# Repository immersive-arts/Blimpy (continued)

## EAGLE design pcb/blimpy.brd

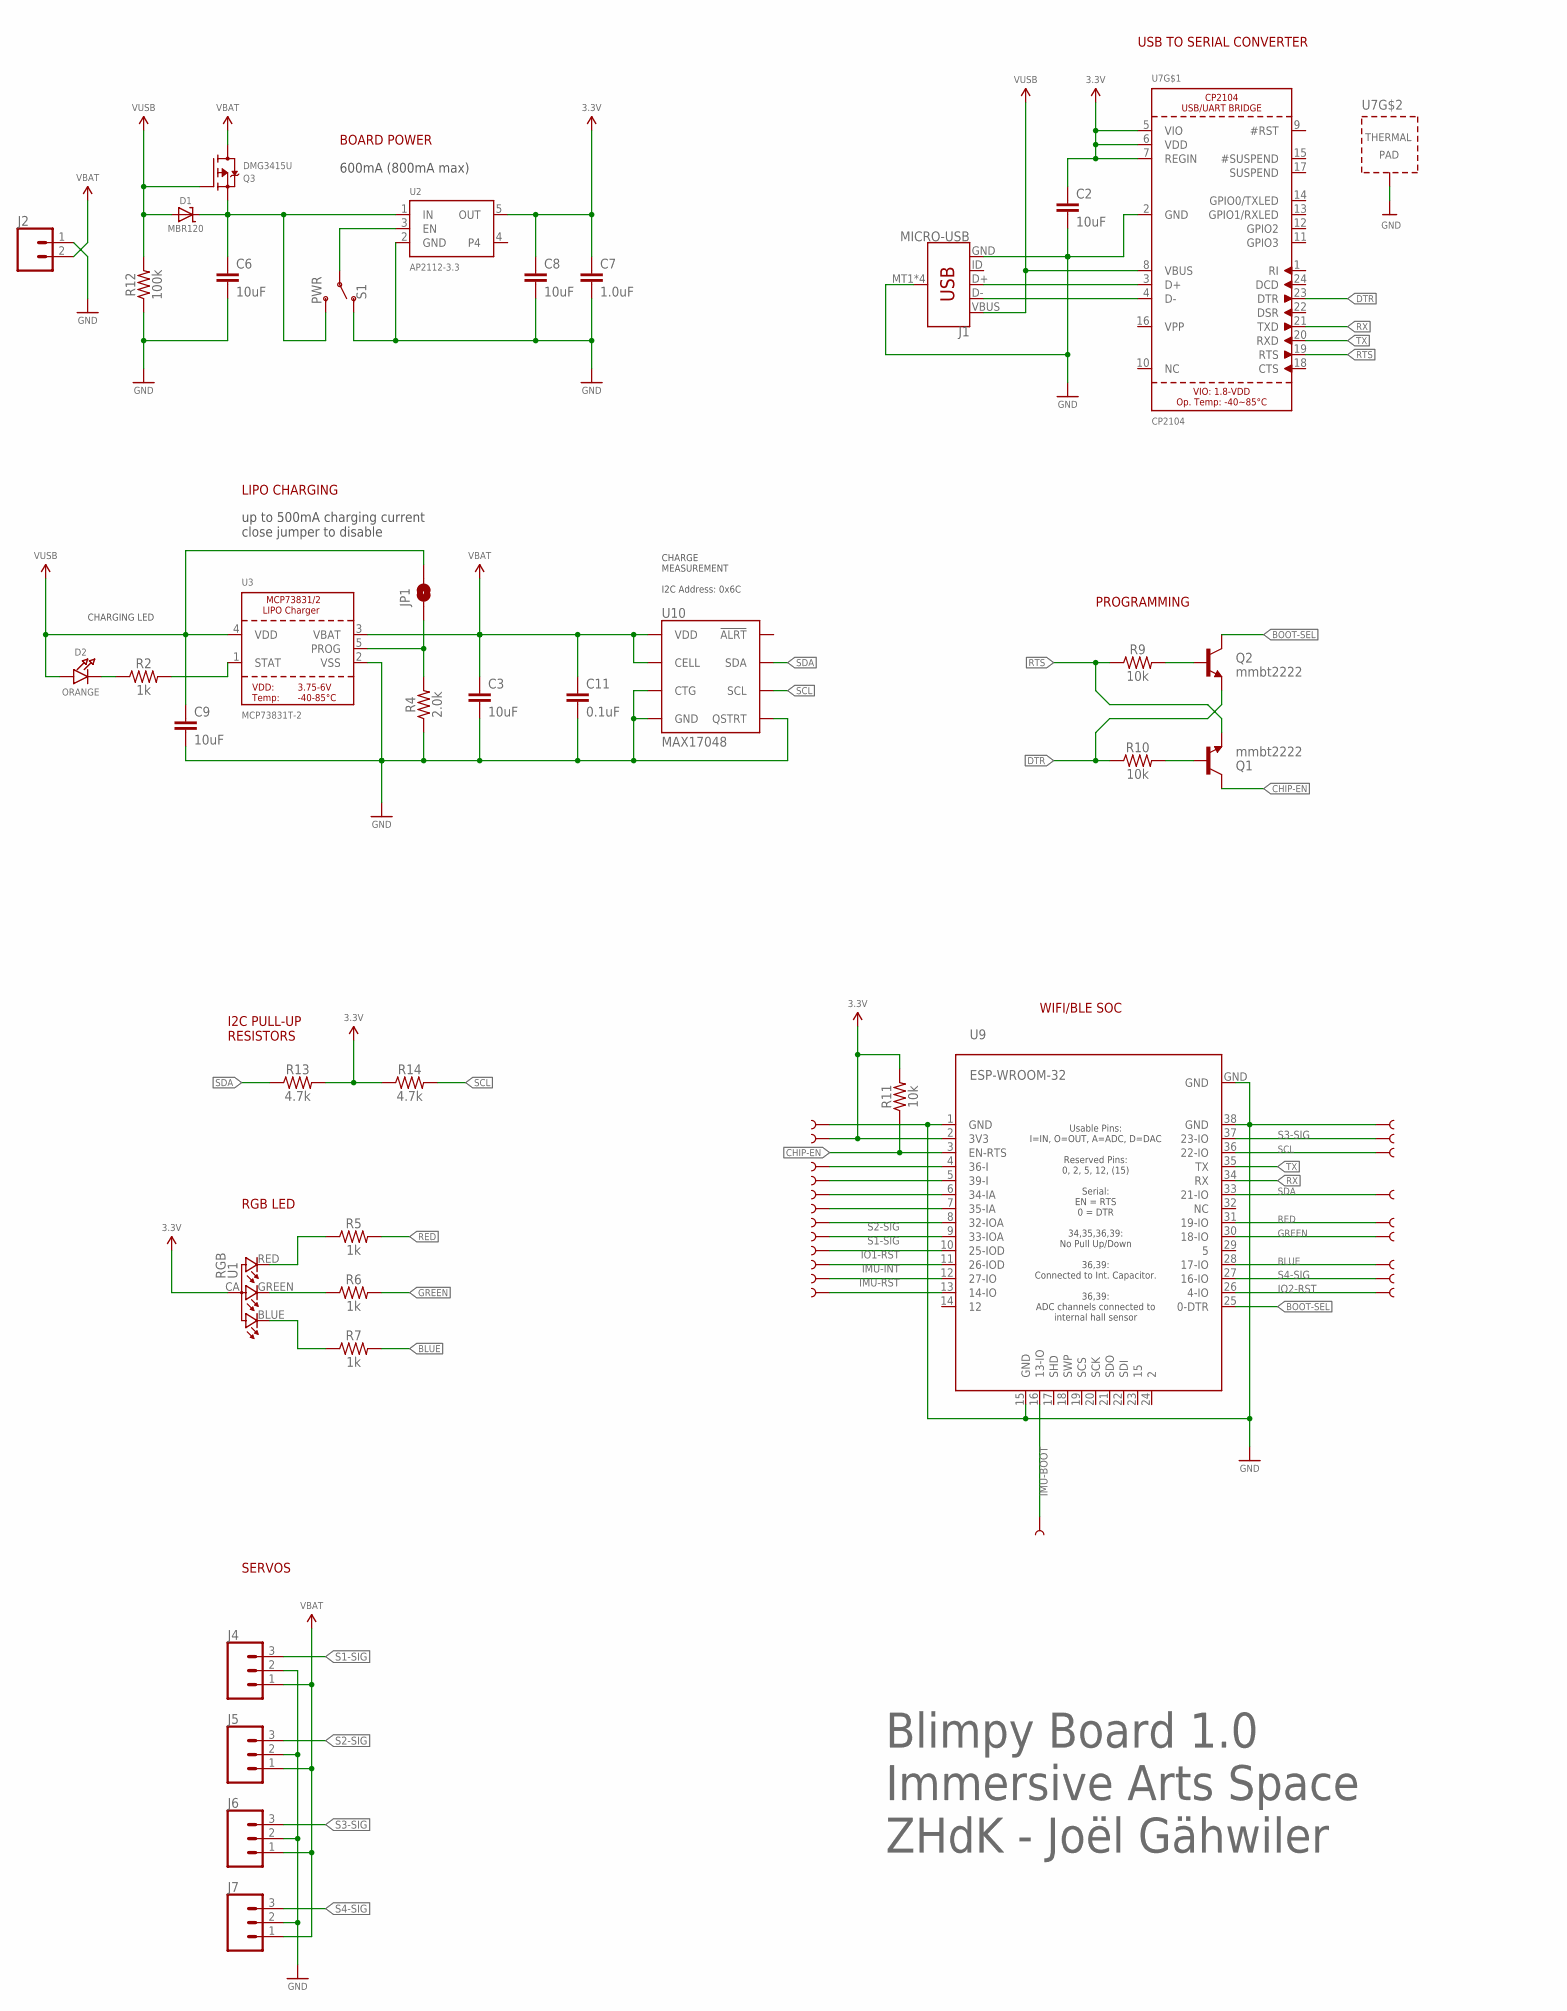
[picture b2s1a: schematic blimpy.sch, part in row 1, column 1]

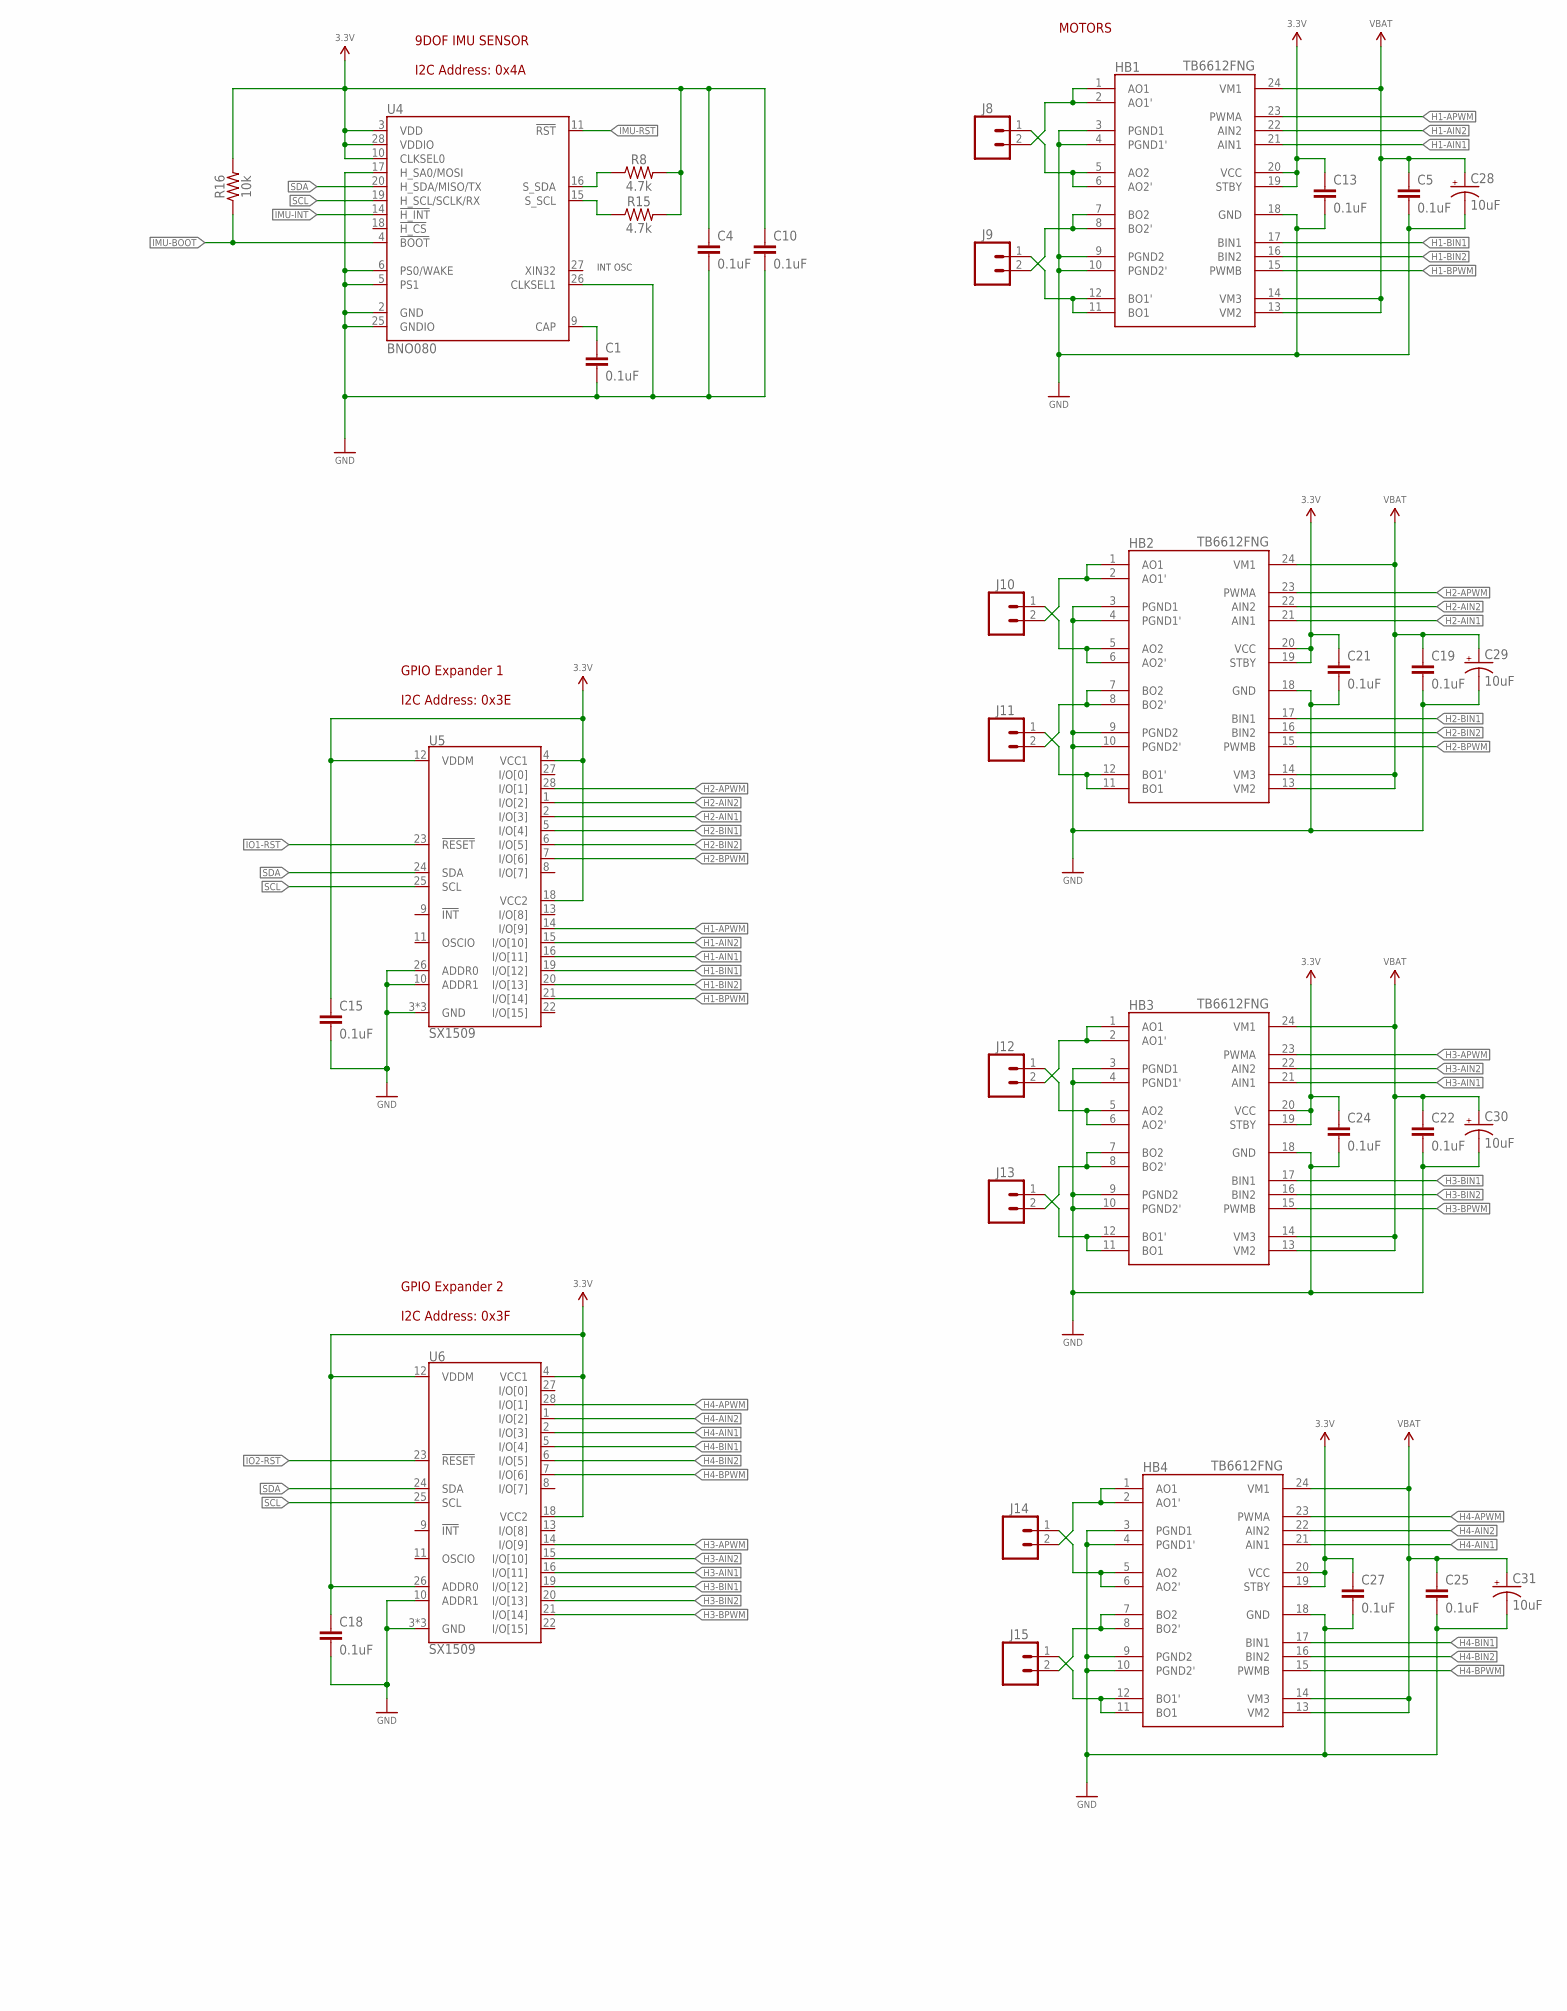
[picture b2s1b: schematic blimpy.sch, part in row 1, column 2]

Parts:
C1, C4, C5, C10, C11, C13, C15, C18, C19, C21, C22, C24, C25, C27: 0.1uF; 0603
C2, C3, C6, C8, C9: 10uF; 0603
C7: 1.0uF; 0603
C28, C29, C30, C31: 10uF; EIA3216
D1: MBR120; SOD-123
D2: ORANGE; CHIPLED_0805_NOOUTLINE
HB1, HB2, HB3, HB4: TB6612FNG; SSOP24
J1: MICRO-USB; USB-MICROB
J2, J8, J9, J10, J11, J12, J13, J14, J15: CONN_02-JST-2MM-SMT; JST-2-SMD
J4, J5, J6, J7: 3-PIN SMD; JST-3-SMD
JP1: JUMPER-SMT_2_NO_SILK; SMT-JUMPER_2_NO_SILK
Q1, Q2: mmbt2222; SOT23-3
Q3: DMG3415U; SOT23-R
R2, R5, R6, R7: 1k; 0603
R4: 2.0k; 0603
R8, R13, R14, R15: 4.7k; 0603
R9, R10, R11, R16: 10k; 0603
R12: 100k; 0603
S1: PWR; SWITCH_SPST_SMD_A
TP1, TP2, TP3, TP4, TP5, TP6, TP7, TP8, TP9, TP10, TP11, TP12, TP13, TP14, TP15, TP16, TP17, TP18, TP19, TP20, TP21, TP22: TEST-POINT3; PAD.03X.03
U1: RGB; PLCC4-2MM-RGB
U2: AP2112-3.3; SOT23-5
U3: MCP73831T-2; SOT23-5
U4: BNO080; LGA-28
U5, U6: SX1509; QFN-28
U7: CP2104; QFN24_4MM_SMSC
U9: ESP-WROOM-32
U10: MAX17048; DFN-8

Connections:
3.3V: C2.1, C4.1, C7.1, C8.1, C10.1, C13.1, C15.1, C18.1, C21.1, C24.1, C27.1, HB1.19 (STBY), HB1.20 (VCC), HB2.19 (STBY), HB2.20 (VCC), HB3.19 (STBY), HB3.20 (VCC), HB4.19 (STBY), HB4.20 (VCC), R8.2, R11.2, R13.2, R14.1, R15.2, R16.2, TP11.P$1, U1.CA (1), U2.5 (OUT), U4.3 (VDD), U4.10 (CLKSEL0), U4.28 (VDDIO), U5.4 (VCC1), U5.12 (VDDM), U5.18 (VCC2), U6.4 (VCC1), U6.12 (VDDM), U6.18 (VCC2), U6.26 (ADDR0), U7.5 (VIO), U7.6 (VDD), U7.7 (REGIN), U9.2 (3V3)
BLUE: R7.2, TP22.P$1, U9.28 (17-IO)
BOOT-SEL: Q2.3 (C), U9.25 (0-DTR)
CHIP-EN: Q1.3 (C), R11.1, U9.3 (EN-RTS)
DTR: Q2.2 (E), R10.1, U7.23 (DTR)
GND: C1.2, C2.2, C3.2, C4.2, C5.2, C6.2, C7.2, C8.2, C9.2, C10.2, C11.2, C13.2, C15.2, C18.2, C19.2, C21.2, C22.2, C24.2, C25.2, C27.2, C28.-, C29.-, C30.-, C31.-, HB1.3 (PGND1), HB1.4 (PGND1'), HB1.9 (PGND2), HB1.10 (PGND2'), HB1.18 (GND), HB2.3 (PGND1), HB2.4 (PGND1'), HB2.9 (PGND2), HB2.10 (PGND2'), HB2.18 (GND), HB3.3 (PGND1), HB3.4 (PGND1'), HB3.9 (PGND2), HB3.10 (PGND2'), HB3.18 (GND), HB4.3 (PGND1), HB4.4 (PGND1'), HB4.9 (PGND2), HB4.10 (PGND2'), HB4.18 (GND), J1.GND, J1.MT1 (SHIELD), J1.MT2 (SHIELD), J1.P$1 (SHIELD), J1.P$2 (SHIELD), J2.1 (2), J4.2, J5.2, J6.2, J7.2, R4.1, R12.1, S1.1 (O), TP12.P$1, TP13.P$1, U2.2 (GND), U3.2 (VSS), U4.2 (GND), U4.5 (PS1), U4.6 (PS0/WAKE), U4.17 (H_SA0/MOSI), U4.25 (GNDIO), U4.26 (CLKSEL1), U5.3 (GND), U5.10 (ADDR1), U5.17 (GND), U5.26 (ADDR0), U5.29 (GND), U6.3 (GND), U6.10 (ADDR1), U6.17 (GND), U6.29 (GND), U7.2 (GND), U7.THERM (TP), U9.1 (GND), U9.15 (GND), U9.38 (GND), U9.GND, U10.P$1 (CTG), U10.P$4 (GND), U10.P$6 (QSTRT), U10.P$9 (GND)
GREEN: R6.2, TP21.P$1, U9.30 (18-IO)
H1-AIN1: HB1.21 (AIN1), U5.16 (I/O[11])
H1-AIN2: HB1.22 (AIN2), U5.15 (I/O[10])
H1-APWM: HB1.23 (PWMA), U5.14 (I/O[9])
H1-BIN1: HB1.17 (BIN1), U5.19 (I/O[12])
H1-BIN2: HB1.16 (BIN2), U5.20 (I/O[13])
H1-BPWM: HB1.15 (PWMB), U5.21 (I/O[14])
H2-AIN1: HB2.21 (AIN1), U5.2 (I/O[3])
H2-AIN2: HB2.22 (AIN2), U5.1 (I/O[2])
H2-APWM: HB2.23 (PWMA), U5.28 (I/O[1])
H2-BIN1: HB2.17 (BIN1), U5.5 (I/O[4])
H2-BIN2: HB2.16 (BIN2), U5.6 (I/O[5])
H2-BPWM: HB2.15 (PWMB), U5.7 (I/O[6])
H3-AIN1: HB3.21 (AIN1), U6.16 (I/O[11])
H3-AIN2: HB3.22 (AIN2), U6.15 (I/O[10])
H3-APWM: HB3.23 (PWMA), U6.14 (I/O[9])
H3-BIN1: HB3.17 (BIN1), U6.19 (I/O[12])
H3-BIN2: HB3.16 (BIN2), U6.20 (I/O[13])
H3-BPWM: HB3.15 (PWMB), U6.21 (I/O[14])
H4-AIN1: HB4.21 (AIN1), U6.2 (I/O[3])
H4-AIN2: HB4.22 (AIN2), U6.1 (I/O[2])
H4-APWM: HB4.23 (PWMA), U6.28 (I/O[1])
H4-BIN1: HB4.17 (BIN1), U6.5 (I/O[4])
H4-BIN2: HB4.16 (BIN2), U6.6 (I/O[5])
H4-BPWM: HB4.15 (PWMB), U6.7 (I/O[6])
HB1-A1: HB1.1 (AO1), HB1.2 (AO1'), J8.2 (1)
HB1-A2: HB1.5 (AO2), HB1.6 (AO2'), J8.1 (2)
HB1-B1: HB1.11 (BO1), HB1.12 (BO1'), J9.1 (2)
HB1-B2: HB1.7 (BO2), HB1.8 (BO2'), J9.2 (1)
HB2-A1: HB2.1 (AO1), HB2.2 (AO1'), J10.2 (1)
HB2-A2: HB2.5 (AO2), HB2.6 (AO2'), J10.1 (2)
HB2-B1: HB2.11 (BO1), HB2.12 (BO1'), J11.1 (2)
HB2-B2: HB2.7 (BO2), HB2.8 (BO2'), J11.2 (1)
HB3-A1: HB3.1 (AO1), HB3.2 (AO1'), J12.2 (1)
HB3-A2: HB3.5 (AO2), HB3.6 (AO2'), J12.1 (2)
HB3-B1: HB3.11 (BO1), HB3.12 (BO1'), J13.1 (2)
HB3-B2: HB3.7 (BO2), HB3.8 (BO2'), J13.2 (1)
HB4-A1: HB4.1 (AO1), HB4.2 (AO1'), J14.2 (1)
HB4-A2: HB4.5 (AO2), HB4.6 (AO2'), J14.1 (2)
HB4-B1: HB4.11 (BO1), HB4.12 (BO1'), J15.1 (2)
HB4-B2: HB4.7 (BO2), HB4.8 (BO2'), J15.2 (1)
IMU-BOOT: R16.1, TP17.P$1, U4.4 (!BOOT), U9.16 (13-IO)
IMU-INT: TP4.P$1, U4.14 (!H_INT), U9.11 (26-IOD)
IMU-RST: TP5.P$1, U4.11 (!RST), U9.12 (27-IO)
IO1-RST: TP3.P$1, U5.23 (!RESET), U9.10 (25-IOD)
IO2-RST: TP16.P$1, U6.23 (!RESET), U9.26 (4-IO)
unnamed: D2.C, R2.1
unnamed: J1.D+, U7.3 (D+)
unnamed: R2.2, U3.1 (STAT)
unnamed: JP1.1, R4.2, U3.5 (PROG)
unnamed: J1.D-, U7.4 (D-)
unnamed: C6.1, D1.C, Q3.2 (S), S1.3 (S), U2.1 (IN)
unnamed: S1.2, U2.3 (EN)
unnamed: R5.1, U1.RED (4)
unnamed: R7.1, U1.BLUE (2)
unnamed: R6.1, U1.GREEN (3)
unnamed: Q1.1 (B), R10.2
unnamed: Q2.1 (B), R9.2
unnamed: R8.1, U4.16 (S_SDA)
unnamed: R15.1, U4.15 (S_SCL)
unnamed: C1.1, U4.9 (CAP)
unnamed: TP10.P$1, U9.4 (36-I)
unnamed: TP9.P$1, U9.5 (39-I)
unnamed: TP8.P$1, U9.6 (34-IA)
unnamed: TP7.P$1, U9.7 (35-IA)
unnamed: TP6.P$1, U9.13 (14-IO)
RED: R5.2, TP20.P$1, U9.31 (19-IO)
RTS: Q1.2 (E), R9.1, U7.19 (RTS)
RX: U7.21 (TXD), U9.34 (RX)
S1-SIG: J4.3, TP2.P$1, U9.9 (33-IOA)
S2-SIG: J5.3, TP1.P$1, U9.8 (32-IOA)
S3-SIG: J6.3, TP14.P$1, U9.37 (23-IO)
S4-SIG: J7.3, TP15.P$1, U9.27 (16-IO)
SCL: R14.2, TP18.P$1, U4.19 (H_SCL/SCLK/RX), U5.25 (SCL), U6.25 (SCL), U9.36 (22-IO), U10.P$7 (SCL)
SDA: R13.1, TP19.P$1, U4.20 (H_SDA/MISO/TX), U5.24 (SDA), U6.24 (SDA), U9.33 (21-IO), U10.P$8 (SDA)
TX: U7.20 (RXD), U9.35 (TX)
V_BATT: C3.1, C5.1, C11.1, C19.1, C22.1, C25.1, C28.+, C29.+, C30.+, C31.+, HB1.13 (VM2), HB1.14 (VM3), HB1.24 (VM1), HB2.13 (VM2), HB2.14 (VM3), HB2.24 (VM1), HB3.13 (VM2), HB3.14 (VM3), HB3.24 (VM1), HB4.13 (VM2), HB4.14 (VM3), HB4.24 (VM1), J2.2 (1), J4.1, J5.1, J6.1, J7.1, Q3.3 (D), U3.3 (VBAT), U10.P$2 (CELL), U10.P$3 (VDD)
V_USB: C9.1, D1.A, D2.A, J1.VBUS, JP1.2, Q3.1 (G), R12.2, U3.4 (VDD), U7.8 (VBUS)

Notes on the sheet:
BOARD POWER
up to 500mA charging current close jumper to disable
USB TO SERIAL CONVERTER
LIPO CHARGING
RGB LED
PROGRAMMING
CHARGING LED
CHARGE MEASUREMENT I2C Address: 0x6C
I2C PULL-UP RESISTORS
WIFI/BLE SOC
9DOF IMU SENSOR I2C Address: 0x4A
INT OSC
GPIO Expander 1 I2C Address: 0x3E
GPIO Expander 2 I2C Address: 0x3F
600mA (800mA max)
SERVOS
MOTORS
Blimpy Board 1.0 Immersive Arts Space ZHdK - Joël Gähwiler

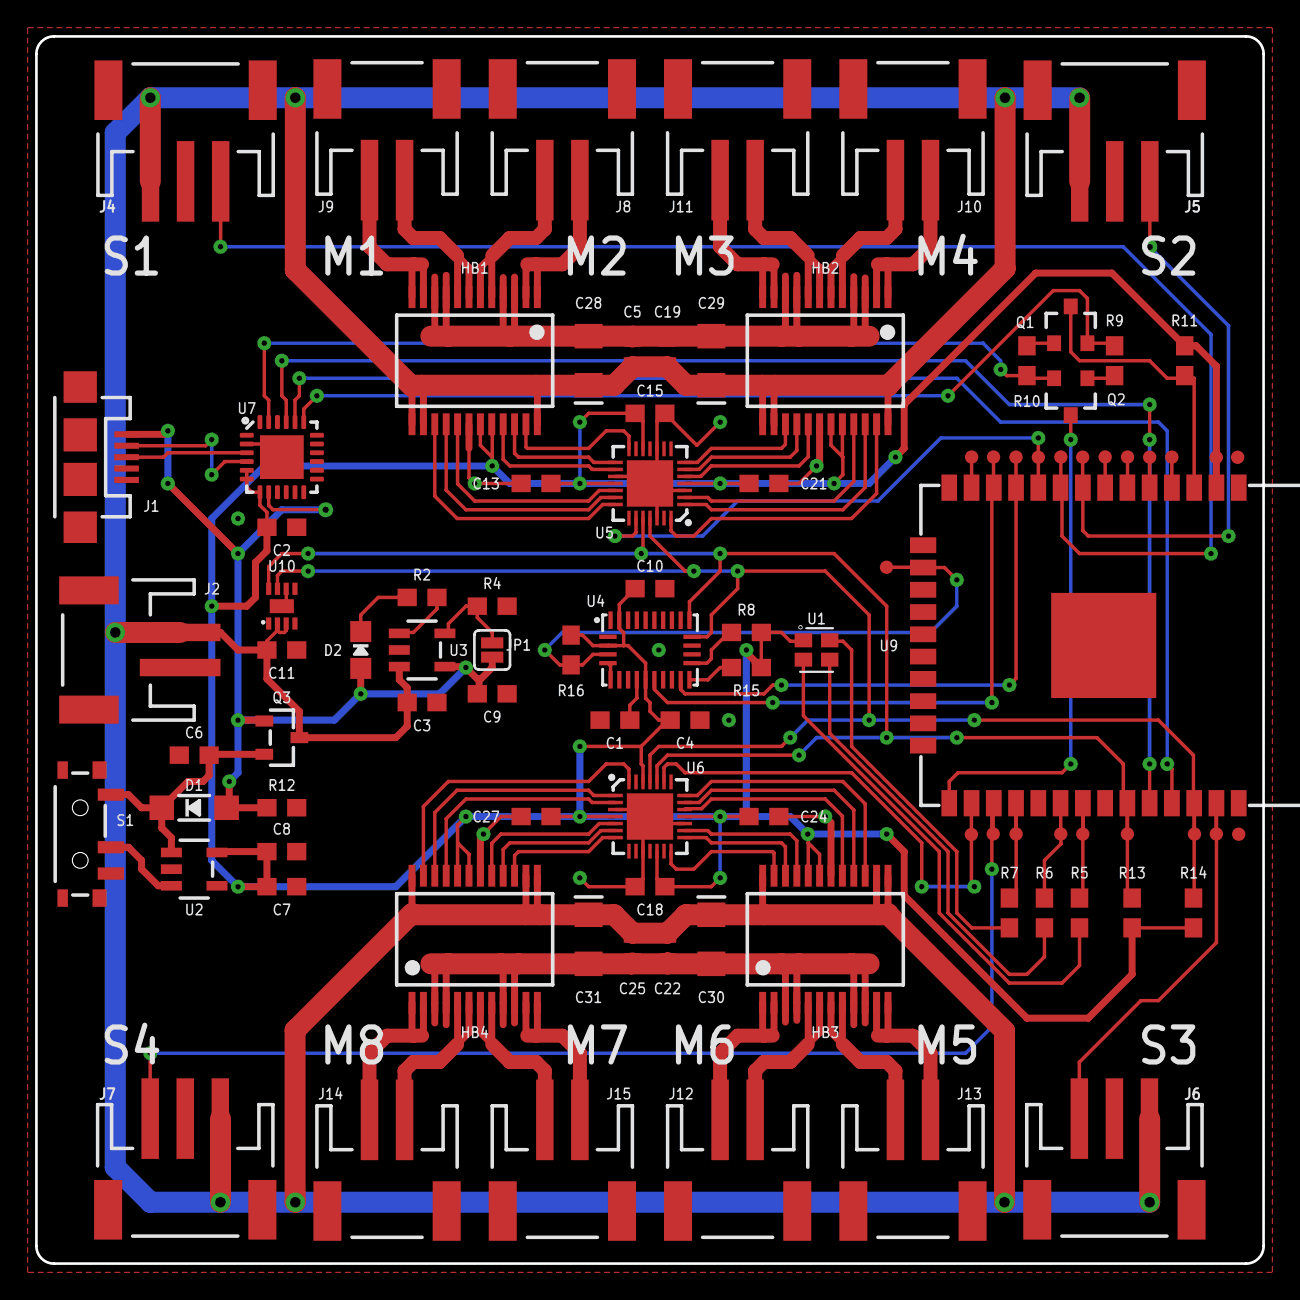
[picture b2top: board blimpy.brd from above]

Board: 2 copper layers, 70.0 x 70.0 mm, 94 parts (0 on the bottom side), 84 nets.

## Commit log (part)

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2019-07-19 added wifi and battery indicators
2019-07-20 fix null pointer
2019-09-12 first pcb iteration
2019-09-13 added settings
2019-09-13 de-invert
2019-09-13 added logo
2019-09-18 updated board design
2019-09-18 added battery gauge
2019-09-18 added address
2019-09-19 removed todo
2019-09-26 improved hbridge traces
2019-09-26 added hbridge gnd traces
2019-09-26 updated hbridge traces and prepared expander
2019-09-26 use 0.2mm traces
2019-09-26 wired io and caps
2019-09-26 fixed io capacitors
2019-09-26 finished hbridge io
2019-09-26 small connections
2019-09-26 updated labels
2019-09-26 reworked main connectors
2019-09-26 downgraded version
2019-09-26 changed setting keys
2019-09-26 replaced usb micro with usb c connector
2019-09-27 shrinked board
2019-09-27 moved stuff into place
2019-09-27 fixed size
2019-09-27 fixed servo pins
2019-09-27 moved in auxillary components
2019-09-27 small fix
2019-09-27 connect imu
2019-09-27 more traces
2019-09-27 show all
2019-09-27 small fixes
2019-09-27 more fixes
2019-09-27 updated vias
2019-09-27 more power traces
2019-09-27 improved power routing
2019-09-27 hide some layers
2019-09-27 connected all components
2019-09-27 finished all traces
2019-09-28 added ground plane and fixed all errors
2019-09-28 changed colors
2019-09-28 fixed
2019-09-28 moved esp
2019-09-28 added text
2019-09-28 updated todo
2019-09-29 routed pogo pins
2019-09-29 moved docs
2019-09-29 bigger ground pads on h bridges
2019-09-29 optimized main battery connections
2019-09-29 rerouted io1-rst
2019-09-29 reduced space
2019-09-29 made more space
2019-09-29 moved led to middle
2019-09-29 updated bom
2019-09-29 added more pogo pins
2019-09-29 added prices
2019-09-30 removed obsolete resistors
2019-09-30 updated docs
2019-09-30 fixed typo
2019-09-30 added awg 28 info
2019-10-07 changed schotky diode to BAT20J
2019-10-07 updated part numbers
2019-10-22 fixed onboard model
2019-10-24 removed not needed duty cycle
2019-10-24 print more stuff
2019-10-24 prototype onboard model calculation
2019-10-24 fix strtok overflow
2019-10-24 free objects
2019-10-24 added comment
2019-10-24 read configuration from parameters
2019-10-24 fix configs
2019-10-24 flip matrix
2019-11-17 read fuel gauge
2019-11-18 new motor control
2019-11-18 disable pullup
2019-11-20 added two motors to model
2019-11-20 use on-board model
2019-11-20 correct controls
2019-11-20 constrain before printing
2019-11-21 added min duty and print fault
2019-11-22 finish dynamic model calculations
2019-11-22 fix model
2019-11-22 use onboard model for calculations
2019-11-23 fix bug
2019-11-25 added servo control
2019-11-25 adde pdfs
2019-11-25 new repo architecture
2019-12-05 prototype manager api
2019-12-09 added max sparck patcher for testing flightpaths
2019-12-12 new speed data fo the drones
2019-12-17 added base topic setting
2019-12-17 choreography three paths
2019-12-17 updated firmware readme
2019-12-17 docs for fanhousing
2019-12-17 mit gif
2019-12-17 updated apps/max and formware documentation
2019-12-17 new pics and main readme
2019-12-17 update pix
2019-12-17 documentation almost finshed. folder name change
2019-12-17 updated main readme
2019-12-17 fanmount print insctructions complete
2019-12-17 gif links added
2019-12-17 new path forms
2019-12-17 path updates
2019-12-18 Added manager
2019-12-18 Added scripts
2019-12-19 Added readme to Manager
2019-12-19 API adjustments
2019-12-20 updated mainreadme
2019-12-20 moved logo to assets
2019-12-20 manager readme adjustments
2019-12-20 added natnet2osc
2020-01-07 added docs
2020-01-07 updated todos
2020-01-07 added mqtt protocol
2020-03-07 added DOI
2020-06-28 Added PCB 2.0
2020-06-29 Added LED connector
2020-06-29 Cosmetic changes
2020-06-30 Motor driver bug fix, added pull-up for btn input, cosmetic changes
2020-07-06 Added jumper to disable charging when MC is running
2020-08-24 fixed typos
2020-08-24 single expander for rgb led
2020-08-24 updated battery
2020-08-24 added power button
2020-08-24 added auto power off
2020-08-24 added new motor control
2020-08-25 even better power button
2020-08-25 added safety off param
2020-08-25 simplified
2020-08-25 added neo pixels
2020-08-25 enabled servos
2020-08-25 fixed motor
2020-08-25 added separate sensitivity
2020-08-25 added battery debugging
2020-08-25 added battery monitoring
2020-08-25 added batter info view
2020-08-25 faster loop
2020-08-26 PCB 2.1 production
2020-08-26 Added revised PCB
2020-08-27 new sparck structure
2020-08-27 fixing sparck patcher
2020-08-27 updated drone controller
2020-08-27 added initial max remote
2020-08-27 Updated scripts for new folder structure
2020-08-27 updated max path controller
2020-08-28 Tuning for pillow
2020-08-28 added motion engine
2020-08-28 fixed rate
2020-08-29 beautified patch
2020-08-29 Added test scripts for manager
2020-08-30 updated blimpy wireless controller app
2020-08-30 improved path calculation
2020-08-30 new more agressive angle correction
2020-08-31 updated DroneController with new ossia node
2020-09-01 added simple osc 2 mqtt bridge
2020-09-01 improved drone controller
2020-09-01 disentangled optitrack tracking data from blimp address
2020-09-02 drone controller for 5 drones
2020-09-03 updated the contoller example to drive 5 drones
2020-09-04 documented mqtt api
2020-09-04 removed leading slash
2020-09-04 documented bluetooth parameters
2020-09-04 bump version
2020-09-06 Added 'hold' and 'goto' feature to manager (not tested)
2020-09-06 Added GUI for manager
2020-09-07 Removed protocol buffer and updated sender example
2020-09-07 Add test publisher for GUI
2020-09-07 Fixed Windows compatibility issue and renamed publisher to test
2020-09-07 Adjusted tuning parameter according to Martin's feedback
2020-09-07 Updated manager README
2020-09-11 Added option to configure tuning parameter remotely
2020-09-11 fix motor data
2020-09-11 Added option to switch between blimps for plotting
2020-09-11 Added option to plot either lines or dots
2020-09-11 some fixes
2020-09-12 Corrected mistake in readme
2020-09-13 Added minimum jerk to alpha
2020-09-13 showready?
2020-10-21 added model publish
2020-10-27 new max package added blender path app
2020-10-28 update to latest natnet2osc and shitr.io reshufling of folder structure adapting starrupscripts to work with relative paths
2020-11-03 rearranged max apps and package and adjusted readme docs to refer to the same naming convention.
2020-11-05 cleanup, rearrange and speedup of BlenderController patch
2020-11-05 fixed inital state of blender remote gui patch
2020-11-05 fixed smal bux with BlenderController and blender - file
2020-11-05 changes to naming conventions for attributes, added more help info
2020-11-05 added flocking example by Lilian Lopez
2020-12-11 fixed bug and implemented functionality
2020-12-11 Manager and GUI interface over MQTT instead of raw UDP
2020-12-11 Restructured manager for constantly sending blimp state (untracked, move, ...)
2021-01-06 updated show file to latest NodeOSC version 2.0.0
2021-03-03 script change due to ip change
2021-04-22 updated startup scripts to include installing needed packages
2021-05-08 update of max patch - blender controller
2021-05-12 updated readme with links to naos documentation
2021-05-16 added new device control abstraction based on javascript
2021-05-31 changed parameters for wheely
2021-06-15 fixed some bugs
2021-06-25 Restructured directories to accommodate different hardware platforms
2021-06-25 Add wheely firmware
2021-06-25 Add shiftr for linux
2021-06-25 Add PCBWay production files
2021-06-25 Fix CMakeLists.txt
2021-06-25 Add original motor controller firmware
2021-06-25 Fix readme
2021-06-25 Add readme for wheely
2021-06-25 fixed parameter settings
2021-06-25 Update readme with electronics connection
2021-06-25 added wheely design files
2021-06-26 added more instructions on connecting motors and electronics
2021-06-26 fixed readme to name the motor controller consitently through the text
2021-08-06 added zenodo info
2021-08-25 Reduce heartbeat rate of manager to 10 Hz
2021-08-25 GUI bugfixes
2021-08-25 update to new API calls
2021-08-25 Update GUI to work with different device_base_topics
2021-08-27 update scripts
2021-09-01 fixes for maxpatch device controller
2021-09-01 Bugfix
2021-09-01 Add 'unmanaged' state when device is removed from manager
2021-09-01 more max-abstraction fixes for device control
2021-09-02 updated max abstractions
2021-09-12 added test patch for motor checks
2021-09-12 re-added lost readme
2021-09-14 API change to accept multiple commands in one MQTT message (fixes asynchronous clear/stack issue)
2021-09-14 Update add/sender/remove example (adds blimp, flies in blimp, removes blimp)
2021-09-14 Add missing angular velocity control
2021-09-15 Upgrade GUI to display state feedback of devices
2021-09-15 Extend feedback message from manager
2021-09-15 Add tuning feature to GUI
2021-09-15 Fix Windows warnings
2021-09-15 Bugfixes
2021-10-13 added motor attachement diagram
2021-10-26 Add brzl config parameters
2021-10-28 Handle unkown device type
2021-10-28 Add unavailable state, and battery charge information to GUI
2021-10-29 Add 3D functionality in manager and GUI for tetrahedron (attitude control not fully working)
2021-11-01 Bugfix in onboard model computation
2021-11-01 disable other peripherals for sound to work
2021-11-01 Body rate computation directly from quaternion
2021-11-01 Change sliders
2021-11-01 Update parameters
2021-11-01 Adjust scripts for tetra branch
2021-11-02 added multi drone control
2021-11-08 Add full 3D attitude control (not represented in API, only through GUI)
2021-11-09 Add 'hack' for tracking an object with 'up' or 'down' orientation
2021-11-09 Bug fix ('i' not assigned)
2021-11-09 Bug fix (parse float if it doesn't have decimals)
2021-12-06 Clarified variable definitions
2021-12-06 Calculate reference velocity if not provided
2021-12-06 Remove body rates reference from 'move' command (doesn't make sense in current controller implementation)
2021-12-06 updated max app to mirror new API changes
2021-12-06 Rename state names and remove 'freeze' state (duplicate with hold)
2021-12-06 Remove roll, pitch, yaw sliders from GUI and clarify variable names
2021-12-06 fixed velocity calc
2021-12-07 repositioning the max patcher window when opening
2021-12-13 updated manager API readme
2021-12-16 added help for fan setup and configuration
2021-12-16 fixed markdown
2021-12-20 Update controller README
2022-03-15 update readme for flashing board
2022-03-17 added new blender inflation simulation file
2022-03-25 added new xbox mapping for osx 12.2
2022-03-25 new processing template and example app for remote control of device
2022-03-28 updated cocoapod project
2022-03-28 limit safety off to 0.5
2022-03-28 Bugfix for 'freeze' command
2022-03-28 Add save button to GUI
2022-03-28 Add scripts folder
2022-04-05 updated help for max
2022-05-04 Add missing protocol stubs
2022-05-04 Add missing app icon assets
2023-03-17 Update wheely controller for new omniwheel platform
2023-05-16 Update to latest naos version
2023-09-18 update motor check patch
2023-11-15 reflect changes to dependencies
2023-11-15 removed streamy
2023-11-15 more small fixes
2023-11-15 added missing sub systems
2023-11-15 updated Podfile
2023-11-15 added missing error checks
2023-11-15 small type fix
2023-11-15 added missing .gitignore
2023-11-15 upgraded wheely firmware versions
2023-11-15 updated ios remote dependencies
2023-11-15 fix warning
2023-11-15 fixed SPI mode
2023-11-15 activated NAOS manager
2023-11-15 fixed bug
2023-11-16 Fix bug when vmax is larger than loop_period in park command
2023-11-16 adjusted readme
2023-11-16 updated readme to latest firmware GUI
2023-11-16 updated abstraction to deal with new controller parameters
2023-11-16 updated desktop links
2023-11-16 Add battery topic to wheely (always 0.0)
2023-11-16 Add attitude reference ramp during parking
2023-11-16 Add wheely nuttx firmware
2023-11-16 added note about "--alt" flag
2024-02-14 update readme to include hint about pressing the button to flash
2024-04-09 renamed file - causes errors on windows machines
2024-05-22 update to new IP addresses
2024-09-25 using local python environment
2024-09-25 changed wheely device controller parameter
